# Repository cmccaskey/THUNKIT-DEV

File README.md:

# About #

Thunkit Electronics sells development boards and tools for hobbyists and engineers alike. Available at [thunkitelectronics.com](https://thunkitelectronics.com) and [Tindie](https://www.tindie.com/stores/cmccaskey). All designs are open source with schematics, board layouts, code, and BOMs freely available.

## In This Repository ##
| ATmega32U2 Development | SPI-LED | USB-UART |
| ------------------------------------------ | ----------------------------------------- | ----------------------------------------- |
|  |  |  |
| ATmega32U2 dev board. Uses Atmel's USB bootloader. | SPI visualizer or multipurpose 8 LED display | 3.3V USB to UART adapter w/ regulator |

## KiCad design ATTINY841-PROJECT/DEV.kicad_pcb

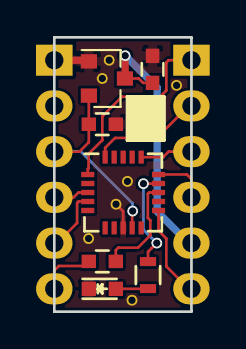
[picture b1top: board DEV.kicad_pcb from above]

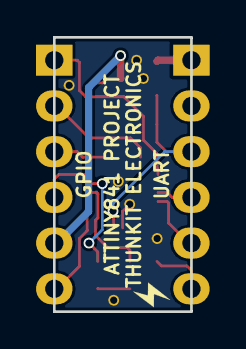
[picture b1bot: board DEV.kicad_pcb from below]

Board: 2 copper layers, 7.6 x 15.2 mm, 9 parts (2 on the bottom side), 14 nets.

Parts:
C1, C2, C3: C; C_0603
D1: LED; LED_0603
P1: UART; Pin_Header_Straight_1x06_NO_SILK
P2: GPIO; Pin_Header_Straight_1x06_NO_SILK
R1: R; R_0603
U1: ATTINY841-MU; QFN-20-1EP_4x4mm_Pitch0.5mm
U2: AP1117; SOT-23

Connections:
GND: C2.2, C3.2, D1.1, P1.1, U1.8, U2.1
MISO: P2.2, U1.20
MOSI: P2.3, U1.16
unnamed: C1.2, U1.13
unnamed: D1.2, R1.1
unnamed: R1.2, U1.14
PA7: P2.4, U1.15
PB0: P2.6, U1.11
RTS: C1.1, P1.6
RX_T841: P1.4, U1.3
SCK: P2.1, U1.1
TX_T841: P1.5, U1.4
VCC: C3.1, P1.3, U1.9, U2.2
VIN: C2.1, P2.5, U2.3

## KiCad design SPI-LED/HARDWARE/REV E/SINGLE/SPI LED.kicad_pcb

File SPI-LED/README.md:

# About #

Thunkit Electronics sells electronic kits for hobbyists and engineers alike. Available at [thunkitelectronics.com](https://thunkitelectronics.com) and [Tindie](https://www.tindie.com/stores/cmccaskey). All designs are open source with schematics, board layouts, code, and BOMs freely available.

## Description ###
 <br />
The SPI-LED is a useful tool for SPI debugging without the use of an oscilloscope. This board is to be wired into MOSI or MISO and SCK and will display on the 8 LEDs on the fron what data is being transferred on that line. With a few delay statements in your program, it is possible to slow the SPI transfers down slow enough that you can visually see whats happening. Since this board does not require a chip select, a single board can be used to monitor MOSI or MISO on your project without requiring a board for each connected device. Additionally, this board can be used in your project if you need a simple 8 bit bar graph to use as an indicator.

## Device ##
This board is based around the 74HC624 shift register. Because of this, this board can be used to debug logic levels ranging from 2 to 6V. Red LEDs allow the board to function down to 2V because of their low forward voltage. Note: the male headers do not come pre-soldered to the board.

## Schematic ##

## Bill of Material ##
[Available Here](IMAGES/SPI-LED_BOM.html)

## Code Example ##
[Available Here](FIRMWARE/SPI-LED/SPI-LED.ino)

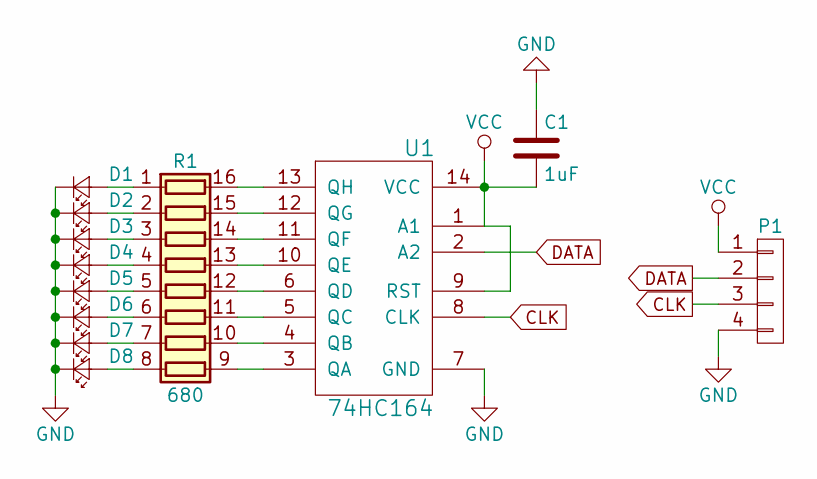
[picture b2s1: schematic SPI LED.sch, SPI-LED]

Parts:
C1: 1uF; C_0603
D1, D2, D3, D4, D5, D6, D7, D8: RED; LED_0603
P1: CONN_01X04; Pin_Header_Straight_1x04_Pitch2.54mm
R1: 680; R_Array_Convex_8x0602
U1: 74HC164; TSSOP-14_4.4x5mm_Pitch0.65mm

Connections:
CLK: P1.3, U1.8 (CLK)
DATA: P1.2, U1.2 (A2)
GND: C1.1, D1.1 (K), D2.1 (K), D3.1 (K), D4.1 (K), D5.1 (K), D6.1 (K), D7.1 (K), D8.1 (K), P1.4, U1.7 (GND)
unnamed: D1.2 (A), R1.1 (R1.1)
unnamed: D2.2 (A), R1.2 (R2.1)
unnamed: D3.2 (A), R1.3 (R3.1)
unnamed: D4.2 (A), R1.4 (R4.1)
unnamed: D5.2 (A), R1.5 (R5.1)
unnamed: D6.2 (A), R1.6 (R6.1)
unnamed: D7.2 (A), R1.7 (R7.1)
unnamed: D8.2 (A), R1.8 (R8.1)
unnamed: R1.9 (R8.2), U1.3 (QA)
unnamed: R1.10 (R7.2), U1.4 (QB)
unnamed: R1.11 (R6.2), U1.5 (QC)
unnamed: R1.12 (R5.2), U1.6 (QD)
unnamed: R1.13 (R4.2), U1.10 (QE)
unnamed: R1.14 (R3.2), U1.11 (QF)
unnamed: R1.15 (R2.2), U1.12 (QG)
unnamed: R1.16 (R1.2), U1.13 (QH)
VCC: C1.2, P1.1, U1.1 (A1), U1.9 (RST), U1.14 (VCC)

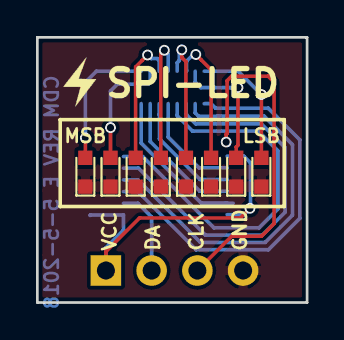
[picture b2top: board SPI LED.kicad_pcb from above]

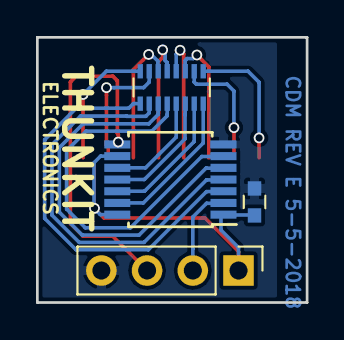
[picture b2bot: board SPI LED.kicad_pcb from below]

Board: 2 copper layers, 15.0 x 14.7 mm, 12 parts (4 on the bottom side), 20 nets.

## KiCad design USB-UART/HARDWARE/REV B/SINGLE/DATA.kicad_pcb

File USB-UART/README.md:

# About #

Thunkit Electronics sells electronic kits for hobbyists and engineers alike. Available at [thunkitelectronics.com](https://thunkitelectronics.com) and [Tindie](https://www.tindie.com/stores/cmccaskey). All designs are open source with schematics, board layouts, code, and BOMs freely available.

## Description ###
 <br />
The USB-UART is a great USB to UART adapter for your electronics projects. It boasts 3.3V only operation with a built in LDO regulator that can output up to 300mA at 3.3V. The built in regulator is a clear advantage over most other FTDI boards that can only output a few mA on the built in voltage regulator. Included on the board is a power LED as well as RX and TX LEDs. The pinout follows the common FTDI cable pinout and a second row of headers allows the board to be stable when plugged into a breadboard. Note: the male headers do not come pre-soldered to the board. Also note that the RX and TX LEDs indicate RX and TX relative to the PC.

## Schematic ##

## Bill of Material ##
[Available Here](IMAGES/USB-UART_BOM.html)

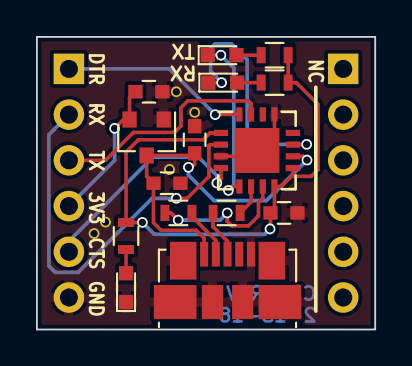
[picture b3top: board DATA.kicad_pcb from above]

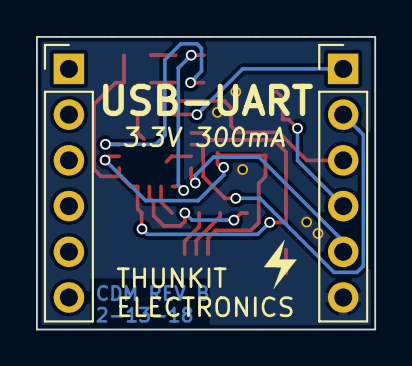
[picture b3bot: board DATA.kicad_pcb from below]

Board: 2 copper layers, 18.8 x 16.3 mm, 17 parts (2 on the bottom side), 17 nets.

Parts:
C1, C2, C3, C4: 1uF; C_0603
D1: LED; LED_0603
D2: TX; LED_0603
D3: RX; LED_0603
P1: USB_OTG; USB_Micro-B_Molex_47346-0001
P2: LEFT; Pin_Header_Straight_1x06_Pitch2.54mm
P3: RIGHT; Pin_Header_Straight_1x06_Pitch2.54mm
R1, R2: 22; R_0603
R3, R4, R5: 330; R_0603
U1: FT230XQ-R; QFN-16-1EP_4x4mm_Pitch0.65mm
U2: AP1117; SOT-23

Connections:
+3V3: C4.1, P2.4, U2.2
+5V: C2.2, C3.1, P1.1, U1.10, U2.3
/D+: P1.3, R2.2
/D-: P1.2, R1.2
/DA+: R2.1, U1.6
/DA-: R1.1, U1.7
CTS: P2.5, U1.4
DTR: P2.1, U1.16
GND: C1.2, C2.1, C3.2, C4.2, D1.1, P1.5, P1.6, P2.6, U1.3, U1.13, U1.17, U2.1
unnamed: D1.2, R3.1
unnamed: D2.1, U1.5
unnamed: D2.2, R4.1
unnamed: D3.1, U1.11
unnamed: D3.2, R5.1
RX: P2.2, U1.2
TX: P2.3, U1.15
VCC: C1.1, R3.2, R4.2, R5.2, U1.1, U1.8, U1.9

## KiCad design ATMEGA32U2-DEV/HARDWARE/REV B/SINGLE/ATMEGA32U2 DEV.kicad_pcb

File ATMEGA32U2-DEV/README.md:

# About #

Thunkit Electronics sells electronic kits for hobbyists and engineers alike. Available at [thunkitelectronics.com](https://thunkitelectronics.com) and [Tindie](https://www.tindie.com/stores/cmccaskey). All designs are open source with schematics, board layouts, code, and BOMs freely available.

## Description ###
 <br />
The ATmega 32U2-Development is a microcontroller development board based around the Atmel ATmega32u2. The ATmega32u2 is a smaller version of the ATmega32u4 used on similar small form development boards. The ATmega32u2 is a great chip to use when a small, low cost, and powerful AVR MCU is needed. The ATmega32u2 comes from the factory with Atmel's DFU USB bootloader. Together the ATmega32u2-Development with avr-gcc and dfu-programmer makes for a great Open Source AVR development experience. C code is also simple to write for this MCU and together with LUFA (USB stack) the USB can be used to emulate numerous devices and interfaces. Note: the male headers do not come pre-soldered to the board.

## Schematic ##

## Bill of Material ##
[Available Here](IMAGES/32U2-DEV_BOM.html)

## Blink Code ##
[Available Here](FIRMWARE/BLINK/BLINK.c)

## Upload Makefile ##
[Available Here](FIRMWARE/BLINK/makefile)

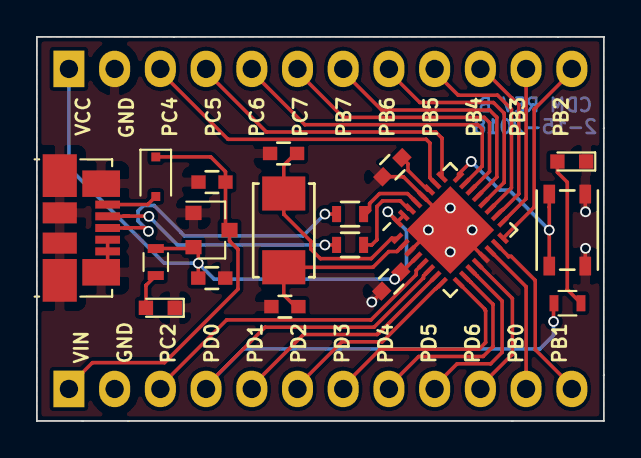
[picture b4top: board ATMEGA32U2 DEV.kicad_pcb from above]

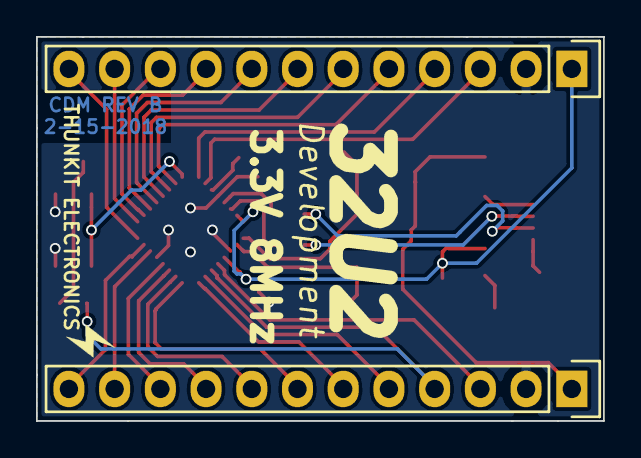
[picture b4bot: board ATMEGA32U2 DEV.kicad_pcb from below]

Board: 2 copper layers, 31.5 x 21.3 mm, 20 parts (2 on the bottom side), 34 nets.

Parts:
C1, C2, C3: C; C_0603
C4, C5, C6: 1uF; C_0603
D1: D_Schottky; D_SOD-323F
D2, D3: RED; LED_0603
P1: USB_A; USB_Micro-B_Molex_47346-0001
P3: HEADER RIGHT; Pin_Header_Straight_1x12
P4: HEADER LEFT; Pin_Header_Straight_1x12
R1, R2: 22; R_0603
R3: 470; R_0603
R4: R; R_0603
SW1: Push_SW; PTS810 SJK 250 SMTR LFS
U1: ATMEGA32U2; QFN-32-1EP_5x5mm_Pitch0.5mm
U2: AP1117; SOT-23
Y1: 8MHz; ABM3

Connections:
+5V: C5.1, D1.1, P4.1, U2.3
GND: C1.2, C2.2, C3.1, C4.1, C5.2, C6.2, D2.1, D3.1, P1.4, P1.5, P3.2, P4.2, SW1.1, U1.3, U1.13, U1.28, U2.1
unnamed: C1.1, U1.1, Y1.1
unnamed: C2.1, U1.2, Y1.2
unnamed: C3.2, U1.27
unnamed: D1.2, P1.1
unnamed: D2.2, R3.2
unnamed: D3.2, R4.1
unnamed: P1.2, R2.2
unnamed: P1.3, R1.2
unnamed: R1.1, U1.29
unnamed: R2.1, U1.30
unnamed: SW1.2, U1.24
PB0: P4.11, U1.14
PB1: P4.12, U1.15
PB2: P3.12, U1.16
PB3: P3.11, U1.17
PB4: P3.10, U1.18
PB5: P3.9, U1.19
PB6: P3.8, U1.20
PB7: P3.7, U1.21
PC2: P4.3, U1.5
PC4: P3.3, U1.26
PC5: P3.4, U1.25
PC6: P3.5, U1.23
PC7: P3.6, U1.22
PD0: P4.4, R3.1, U1.6
PD1: P4.5, U1.7
PD2: P4.6, U1.8
PD3: P4.7, U1.9
PD4: P4.8, U1.10
PD5: P4.9, U1.11
PD6: P4.10, U1.12
VCC: C4.2, C6.1, P3.1, R4.2, U1.4, U1.31, U1.32, U2.2

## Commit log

2018-07-04 init
2018-07-08 adjusted scripts
2018-07-16 Panel updates and removed AX5043
2018-09-09 file recovery and updates
2018-09-10 image typo
2018-09-29 makefile replaces dfuprog
2018-09-30 optimize size
2018-10-01 updated makefile
2018-10-01 makefile comment
2018-10-14 added USB-UART images to readme
2018-10-14 added SPI-LED images and updated readme
2018-10-14 readme typo
2018-10-14 added readme and images
2018-10-14 added global readme
2018-10-14 updated to larger images
2018-10-24 added example code
2018-10-24 spi-led readme update
2018-10-24 readme update
2018-10-24 changed URL
2018-10-24 readme updates
2018-10-24 fixed readme link
2018-10-24 link fix
2018-10-29 added blackbox code
2018-10-29 make clean
2018-11-07 added attiny841
